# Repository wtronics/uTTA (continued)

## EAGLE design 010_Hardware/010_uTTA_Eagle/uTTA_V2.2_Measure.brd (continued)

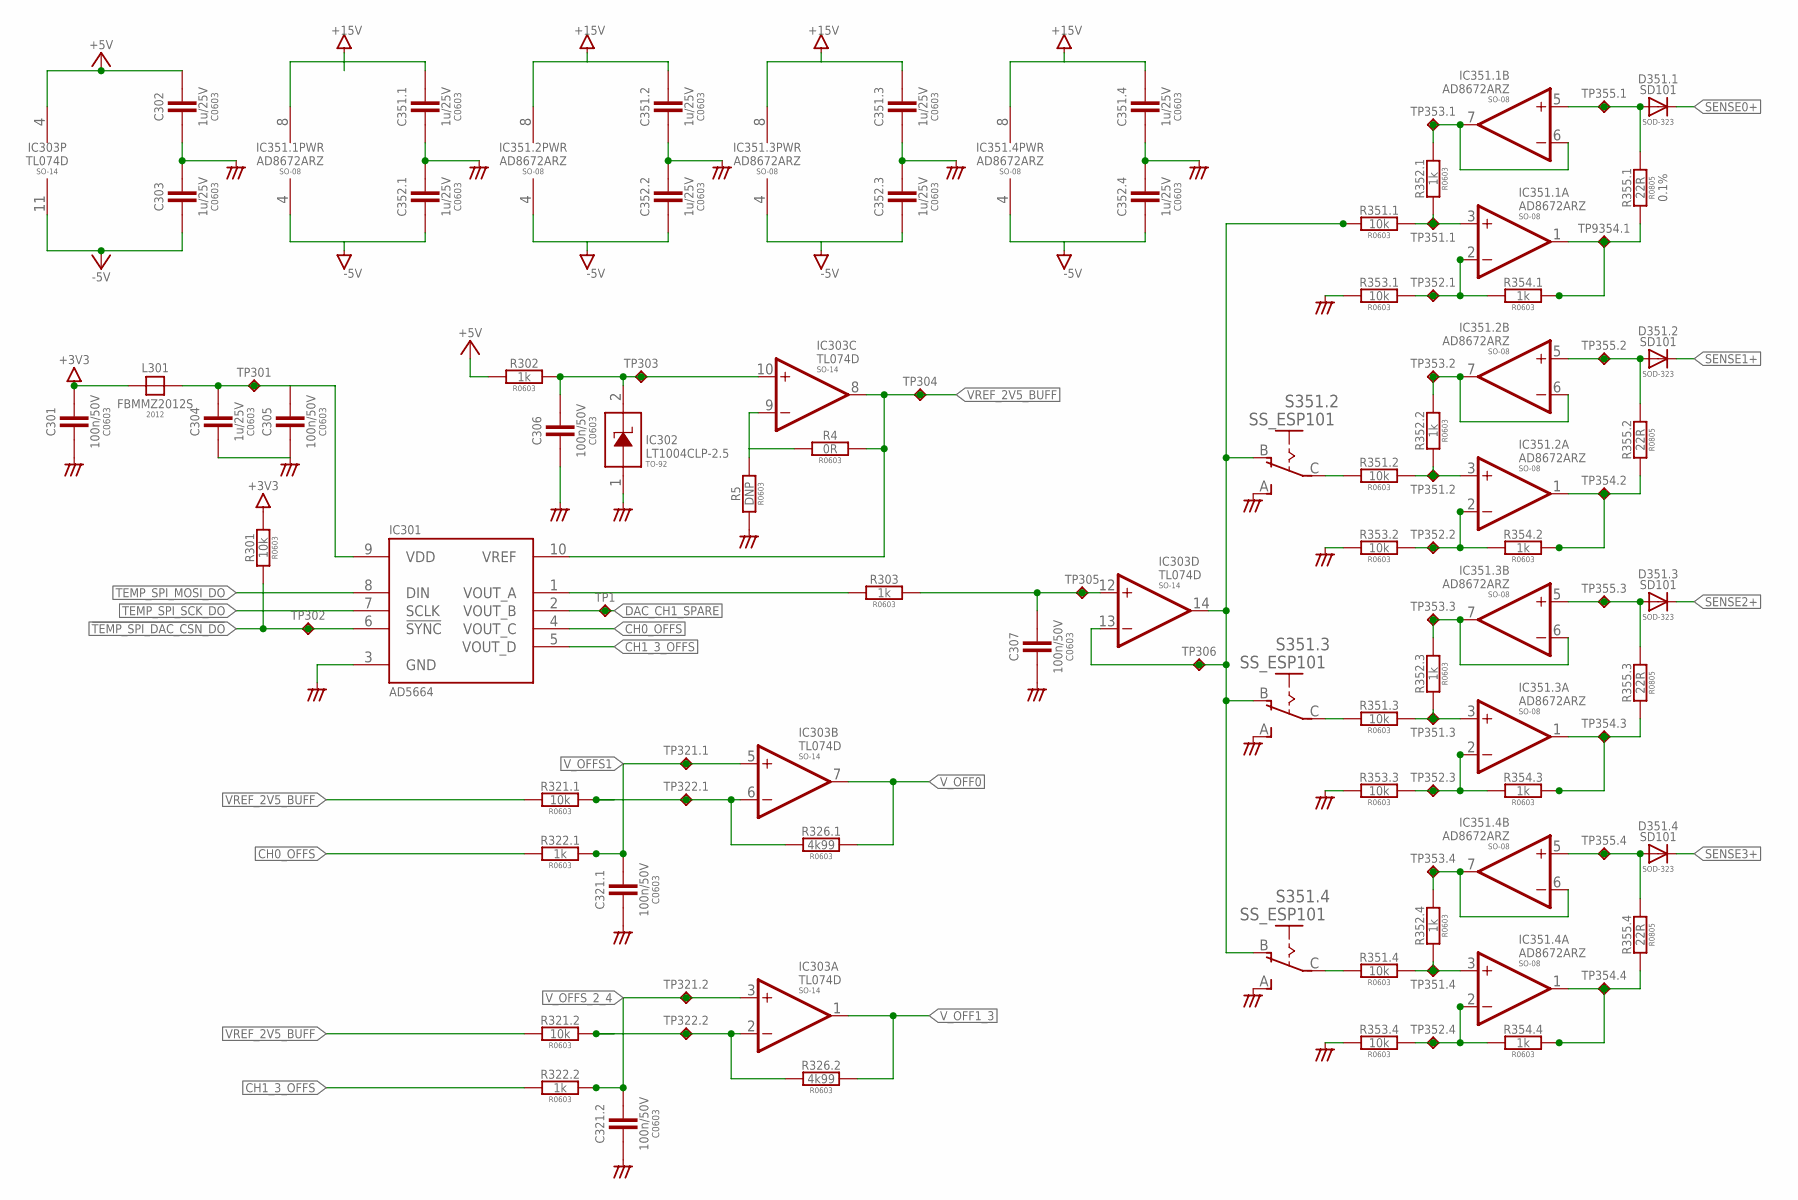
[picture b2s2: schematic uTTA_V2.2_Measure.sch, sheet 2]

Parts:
C301, C305, C306, C307, C321.1, C321.2: 100n/50V; C0603
C302, C303, C304, C351.1, C351.2, C351.3, C351.4, C352.1, C352.2, C352.3, C352.4: 1u/25V; C0603
D351.1, D351.2, D351.3, D351.4: SD101; SOD323-R
IC301: AD5664; MSOP10
IC302: LT1004CLP-2.5; TO92-
IC303: TL074D; SO14
IC351.1, IC351.2, IC351.3, IC351.4: AD8672ARZ; SO08
L301: FBMMZ2012S; FB2012
R4: 0R; R0603
R5: DNP; R0603
R301: 10k; R0603
R302, R303, R322.1, R322.2: 1k; R0603
R321.1, R321.2, R351.1, R351.2, R351.3, R351.4, R353.1, R353.2, R353.3, R353.4: 10k; R0603; TOLERANCE 0.1%
R326.1, R326.2: 4k99; R0603; TOLERANCE 0.1%
R352.1, R352.2, R352.3, R352.4, R354.1, R354.2, R354.3, R354.4: 1k; R0603; TOLERANCE 0.1%
R355.1, R355.2, R355.3, R355.4: 22R; R0805; TOLERANCE 0.1%
S351.2, S351.3, S351.4: SS_ESP101
TP1, TP301, TP302, TP304, TP306, TP321.1, TP321.2, TP322.1, TP322.2, TP351.1, TP351.2, TP351.3, TP351.4, TP352.1, TP352.2, TP352.3, TP352.4, TP353.1, TP353.2, TP353.3, TP353.4, TP354.2, TP354.3, TP354.4, TP355.1, TP355.2, TP355.3, TP355.4, TP9354.1: TPC90; C90
TP303, TP305: TPC90H30; C90H30

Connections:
3V3_DAC: C304.1, C305.1, IC301.9 (VDD), L301.2, TP301.P$1
!TEMP_SPI_DAC_CSN_DO: IC301.6 (!SYNC), R301.2, TP302.P$1; also elsewhere on the board
+3V3: C301.1, L301.1, R301.1; also elsewhere on the board
+5V: C302.1, IC303.4 (V+), R302.1; also elsewhere on the board
+15V: C351.1.1, C351.2.1, C351.3.1, C351.4.1, IC351.1.8 (V+), IC351.2.8 (V+), IC351.3.8 (V+), IC351.4.8 (V+); also elsewhere on the board
-5V: C303.2, C352.1.2, C352.2.2, C352.3.2, C352.4.2, IC303.11 (V-), IC351.1.4 (V-), IC351.2.4 (V-), IC351.3.4 (V-), IC351.4.4 (V-); also elsewhere on the board
AGND: C301.2, C302.2, C303.1, C304.2, C305.2, C306.2, C307.2, C321.1.2, C321.2.2, C351.1.2, C351.2.2, C351.3.2, C351.4.2, C352.1.1, C352.2.1, C352.3.1, C352.4.1, IC301.3 (GND), IC302.1 (A), R5.2, R353.1.1, R353.2.1, R353.3.1, R353.4.1, S351.2.A (S), S351.3.A (S), S351.4.A (S); also elsewhere on the board
CH0_OFFS: IC301.4 (VOUT_C), R322.1.1
CH1_3_OFFS: IC301.5 (VOUT_D), R322.2.1
DAC_CH1_SPARE: IC301.2 (VOUT_B), TP1.P$1
ISENS_SET: IC303.13 (-IN), IC303.14 (OUT), R351.1.1, S351.2.B (O), S351.3.B (O), S351.4.B (O), TP306.P$1
ISENS_SET_IN: C307.1, IC303.12 (+IN), R303.2, TP305.P$1
ISEN_FB1: D351.1.A, IC351.1.5 (+IN), R355.1.2, TP355.1.P$1
ISEN_FB2: D351.2.A, IC351.2.5 (+IN), R355.2.2, TP355.2.P$1
ISEN_FB3: D351.3.A, IC351.3.5 (+IN), R355.3.2, TP355.3.P$1
ISEN_FB4: D351.4.A, IC351.4.5 (+IN), R355.4.2, TP355.4.P$1
ISEN_FB_OUT1: IC351.1.6 (-IN), IC351.1.7 (OUT), R352.1.2, TP353.1.P$1
ISEN_FB_OUT2: IC351.2.6 (-IN), IC351.2.7 (OUT), R352.2.2, TP353.2.P$1
ISEN_FB_OUT3: IC351.3.6 (-IN), IC351.3.7 (OUT), R352.3.2, TP353.3.P$1
ISEN_FB_OUT4: IC351.4.6 (-IN), IC351.4.7 (OUT), R352.4.2, TP353.4.P$1
ISEN_FB_SUM1: IC351.1.2 (-IN), R353.1.2, R354.1.1, TP352.1.P$1
ISEN_FB_SUM2: IC351.2.2 (-IN), R353.2.2, R354.2.1, TP352.2.P$1
ISEN_FB_SUM3: IC351.3.2 (-IN), R353.3.2, R354.3.1, TP352.3.P$1
ISEN_FB_SUM4: IC351.4.2 (-IN), R353.4.2, R354.4.1, TP352.4.P$1
ISEN_OUT1: IC351.1.1 (OUT), R354.1.2, R355.1.1, TP9354.1.P$1
ISEN_OUT2: IC351.2.1 (OUT), R354.2.2, R355.2.1, TP354.2.P$1
ISEN_OUT3: IC351.3.1 (OUT), R354.3.2, R355.3.1, TP354.3.P$1
ISEN_OUT4: IC351.4.1 (OUT), R354.4.2, R355.4.1, TP354.4.P$1
ISEN_SET2: R351.2.1, S351.2.C
ISEN_SET3: R351.3.1, S351.3.C
ISEN_SET4: R351.4.1, S351.4.C
ISEN_SET_SUM1: IC351.1.3 (+IN), R351.1.2, R352.1.1, TP351.1.P$1
ISEN_SET_SUM2: IC351.2.3 (+IN), R351.2.2, R352.2.1, TP351.2.P$1
ISEN_SET_SUM3: IC351.3.3 (+IN), R351.3.2, R352.3.1, TP351.3.P$1
ISEN_SET_SUM4: IC351.4.3 (+IN), R351.4.2, R352.4.1, TP351.4.P$1
I_SENSE_DAC_SET: IC301.1 (VOUT_A), R303.1
unnamed: IC303.9 (-IN), R4.2, R5.1
SENSE0+: D351.1.C; also elsewhere on the board
SENSE1+: D351.2.C; also elsewhere on the board
SENSE2+: D351.3.C; also elsewhere on the board
SENSE3+: D351.4.C; also elsewhere on the board
TEMP_SPI_MOSI_DO: IC301.8 (DIN); also elsewhere on the board
TEMP_SPI_SCK_DO: IC301.7 (SCLK); also elsewhere on the board
VOFFS_RR1: IC303.6 (-IN), R321.1.1, R326.1.2, TP322.1.P$1
VOFFS_RR2_4: IC303.2 (-IN), R321.2.1, R326.2.2, TP322.2.P$1
VREF: C306.1, IC302.2 (C), IC303.10 (+IN), R302.2, TP303.P$1
VREF_2V5_BUFF: IC301.10 (VREF), IC303.8 (OUT), R4.1, R321.1.2, R321.2.2, TP304.P$1; also elsewhere on the board
V_OFF0: IC303.7 (OUT), R326.1.1; also elsewhere on the board
V_OFF1_3: IC303.1 (OUT), R326.2.1; also elsewhere on the board
V_OFFS1: C321.1.1, IC303.5 (+IN), R322.1.2, TP321.1.P$1
V_OFFS_2_4: C321.2.1, IC303.3 (+IN), R322.2.2, TP321.2.P$1

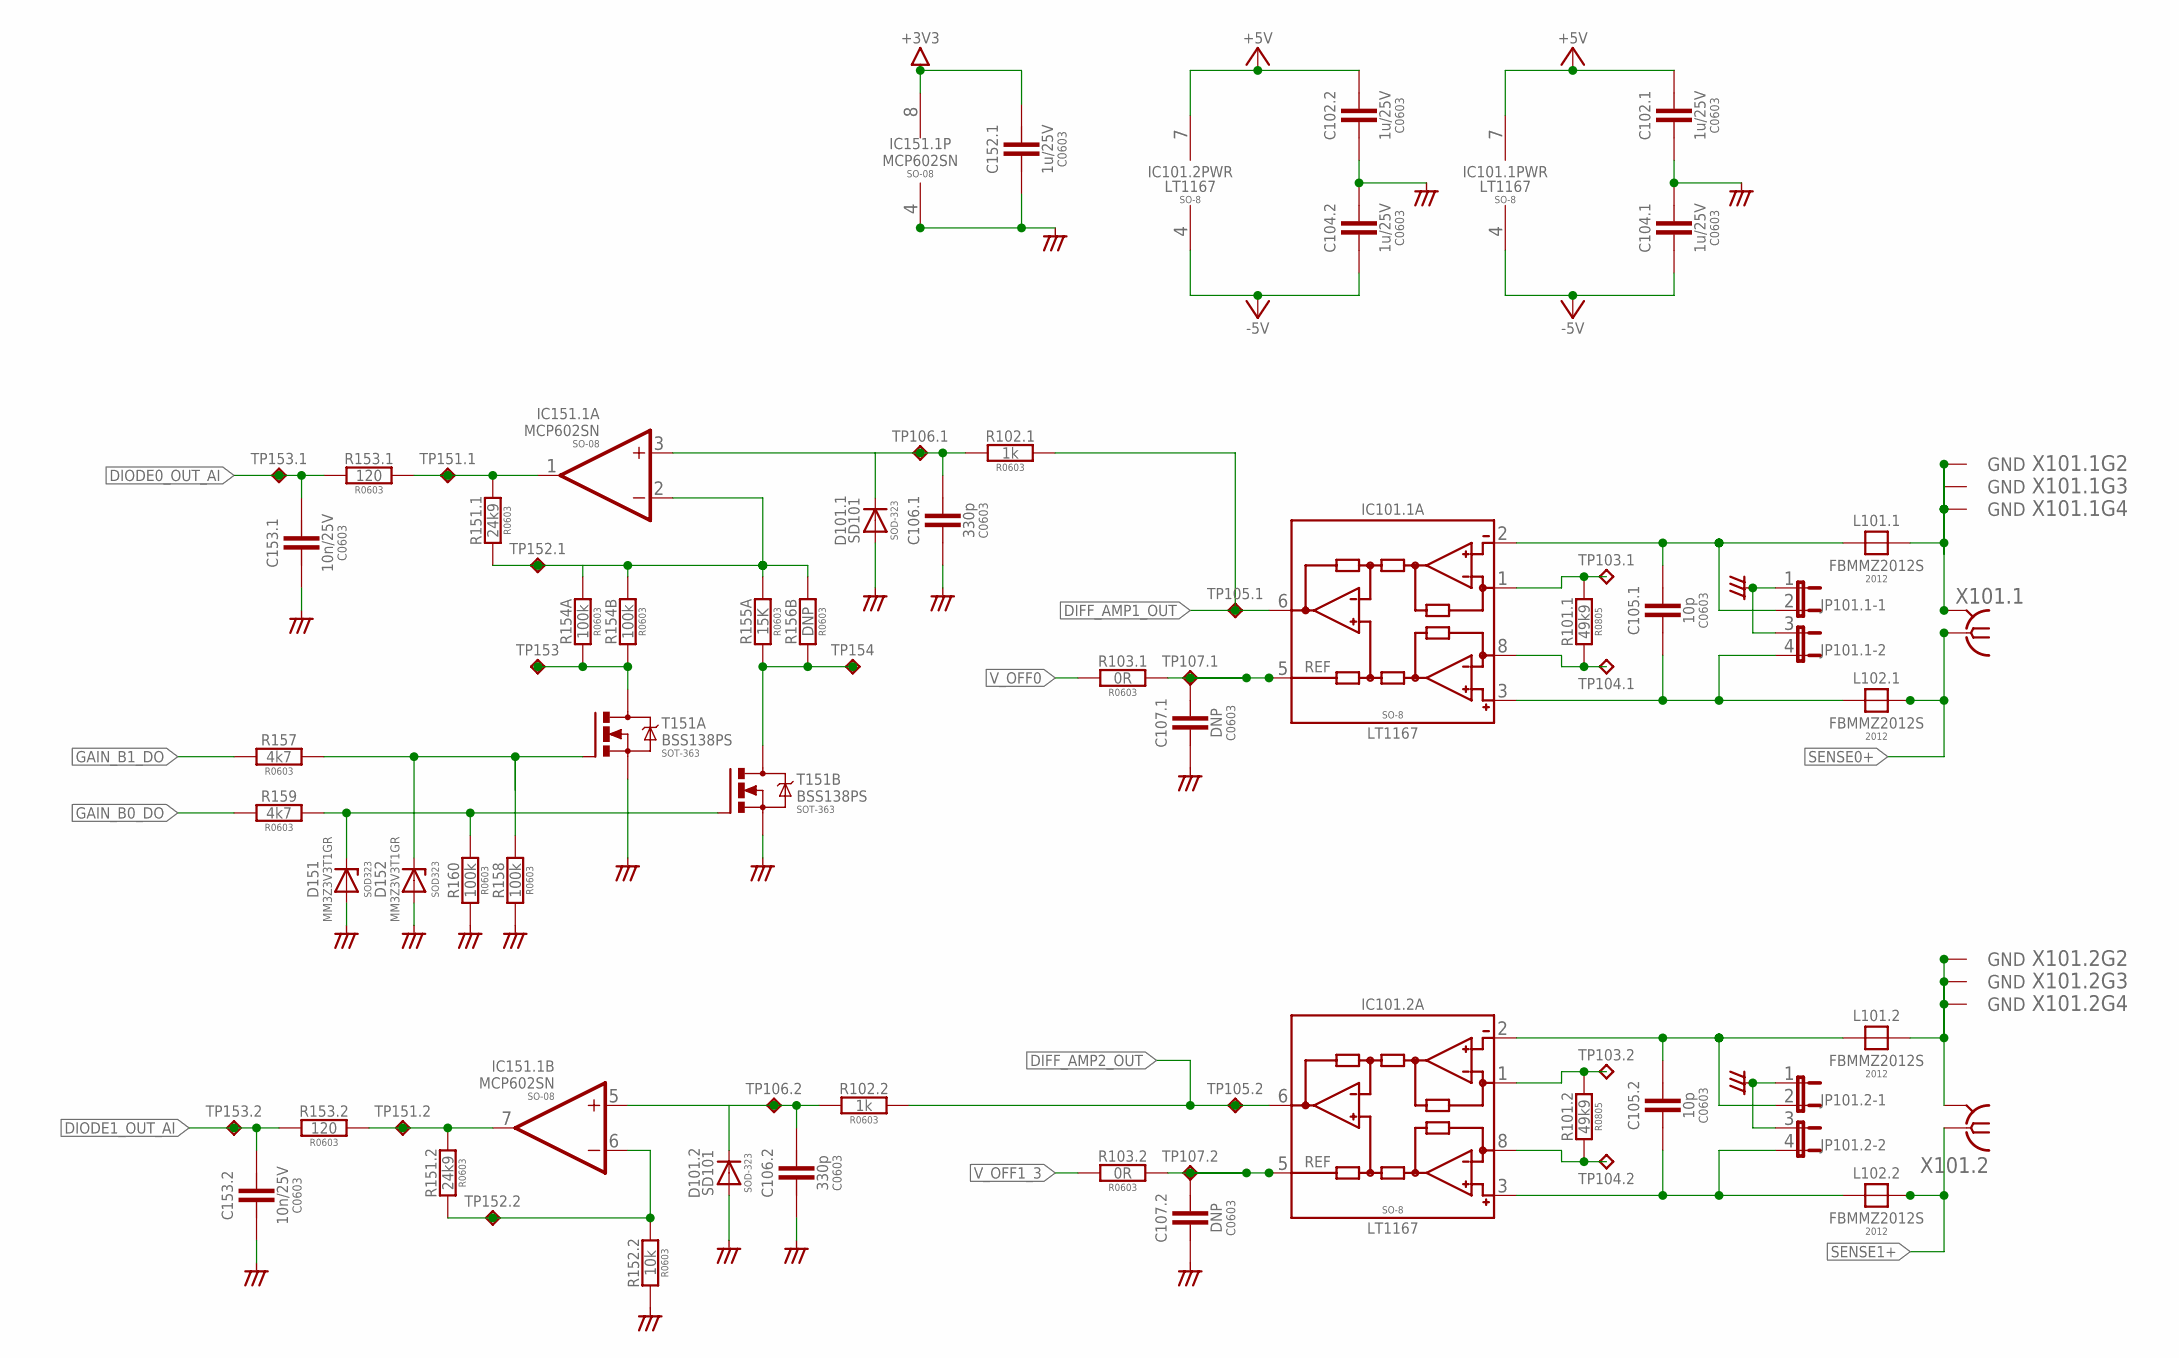
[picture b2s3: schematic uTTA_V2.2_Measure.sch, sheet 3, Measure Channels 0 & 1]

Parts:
C102.1, C102.2, C104.1, C104.2, C152.1: 1u/25V; C0603
C105.1, C105.2: 10p; C0603
C106.1, C106.2: 330p; C0603
C107.1, C107.2: DNP; C0603
C153.1, C153.2: 10n/25V; C0603
D101.1, D101.2: SD101; SOD323-R
D151, D152: MM3Z3V3T1GR; SOD323-R
IC101.1, IC101.2: LT1167; SO08
IC151.1: MCP602SN; SO08
JP101.1, JP101.2: JP2QE; JP2Q
L101.1, L101.2, L102.1, L102.2: FBMMZ2012S; FB2012
R101.1, R101.2: 49k9; R0805; TOLERANCE 0.1%
R102.1, R102.2: 1k; R0603
R103.1, R103.2: 0R; R0603
R151.1, R151.2: 24k9; R0603; TOLERANCE 0.1%
R152.2: 10k; R0603; TOLERANCE 0.1%
R153.1, R153.2: 120; R0603
R154A, R154B: 100k; R0603; TOLERANCE 0.1%
R155A: 15K; R0603; TOLERANCE 0.1%
R156B: DNP; R0603
R157, R159: 4k7; R0603
R158, R160: 100k; R0603
T151: BSS138PS; SOT363_PHILIPS
TP103.1, TP103.2, TP104.1, TP104.2, TP105.1, TP105.2, TP107.1, TP107.2, TP152.1, TP152.2, TP153, TP154: TPC90; C90
TP106.1, TP106.2, TP151.1, TP151.2, TP153.1, TP153.2: TPC90H30; C90H30
X101.1, X101.2: BU-SMA-GSPECIAL; BU_SMA_3P

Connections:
+3V3: C152.1.1, IC151.1.8 (V+); also elsewhere on the board
+5V: C102.1.1, C102.2.1, IC101.1.7 (V+), IC101.2.7 (V+); also elsewhere on the board
-5V: C104.1.2, C104.2.2, IC101.1.4 (V-), IC101.2.4 (V-); also elsewhere on the board
AGND: C102.1.2, C102.2.2, C104.1.1, C104.2.1, C106.1.2, C106.2.2, C107.1.2, C107.2.2, C152.1.2, C153.1.2, C153.2.2, D101.1.A, D101.2.A, D151.A, D152.A, IC151.1.4 (V-), JP101.1.1, JP101.1.3 (1), JP101.2.1, JP101.2.3 (1), R152.2.1, R158.1, R160.1, T151.1 (S), T151.4 (S); also elsewhere on the board
AMP1_OUT: IC151.1.1 (OUT), R151.1.2, R153.1.2, TP151.1.P$1
AMP1_RG_B0: R155A.1, R156B.1, T151.6 (D), TP154.P$1
AMP1_RG_B1: R154A.1, R154B.1, T151.3 (D), TP153.P$1
AMP2_FB: IC151.1.6 (-IN), R151.2.1, R152.2.2, TP152.2.P$1
AMP2_OUT: IC151.1.7 (OUT), R151.2.2, R153.2.2, TP151.2.P$1
B0_GATE: D151.C, R159.2, R160.2, T151.5 (G)
B1_GATE: D152.C, R157.2, R158.2, T151.2 (G)
DIFF_AMP1_OUT: IC101.1.6 (OUT), R102.1.2, TP105.1.P$1
DIFF_AMP2_OUT: IC101.2.6 (OUT), R102.2.2, TP105.2.P$1
DIODE0_OUT_AI: C153.1.1, R153.1.1, TP153.1.P$1; also elsewhere on the board
DIODE1_OUT_AI: C153.2.1, R153.2.1, TP153.2.P$1; also elsewhere on the board
DIODE2_IN: C106.2.1, D101.2.C, IC151.1.5 (+IN), R102.2.1, TP106.2.P$1
GAIN1+: IC101.1.8 (RG), R101.1.2, TP104.1.P$1
GAIN1-: IC101.1.1 (RG), R101.1.1, TP103.1.P$1
GAIN2+: IC101.2.8 (RG), R101.2.2, TP104.2.P$1
GAIN2-: IC101.2.1 (RG), R101.2.1, TP103.2.P$1
GAIN_B0_DO: R159.1; also elsewhere on the board
GAIN_B1_DO: R157.1; also elsewhere on the board
IN1+: C105.1.2, IC101.1.3 (+IN), JP101.1.4 (2), L102.1.1
IN1-: C105.1.1, IC101.1.2 (-IN), JP101.1.2, L101.1.1
IN2+: C105.2.2, IC101.2.3 (+IN), JP101.2.4 (2), L102.2.1
IN2-: C105.2.1, IC101.2.2 (-IN), JP101.2.2, L101.2.1
PGA_DIODE1_IN: C106.1.1, D101.1.C, IC151.1.3 (+IN), R102.1.1, TP106.1.P$1
SENSE0+: L102.1.2, X101.1.C1 (1), X101.1.C2 (1); also elsewhere on the board
SENSE1+: L102.2.2, X101.2.C1 (1), X101.2.C2 (1); also elsewhere on the board
SENSE1-: L101.1.2, X101.1.@GND1 (GND), X101.1.@GND2 (GND), X101.1.@GND3 (GND), X101.1.@GND4 (GND), X101.1.GND
SENSE2-: L101.2.2, X101.2.@GND1 (GND), X101.2.@GND2 (GND), X101.2.@GND3 (GND), X101.2.@GND4 (GND), X101.2.GND
TP152.1: IC151.1.2 (-IN), R151.1.1, R154A.2, R154B.2, R155A.2, R156B.2, TP152.1.P$1
V_OFF0: R103.1.1; also elsewhere on the board
V_OFF1_3: R103.2.1; also elsewhere on the board
V_OPREF1: C107.1.1, IC101.1.5 (REF), R103.1.2, TP107.1.P$1
V_OPREF2: C107.2.1, IC101.2.5 (REF), R103.2.2, TP107.2.P$1

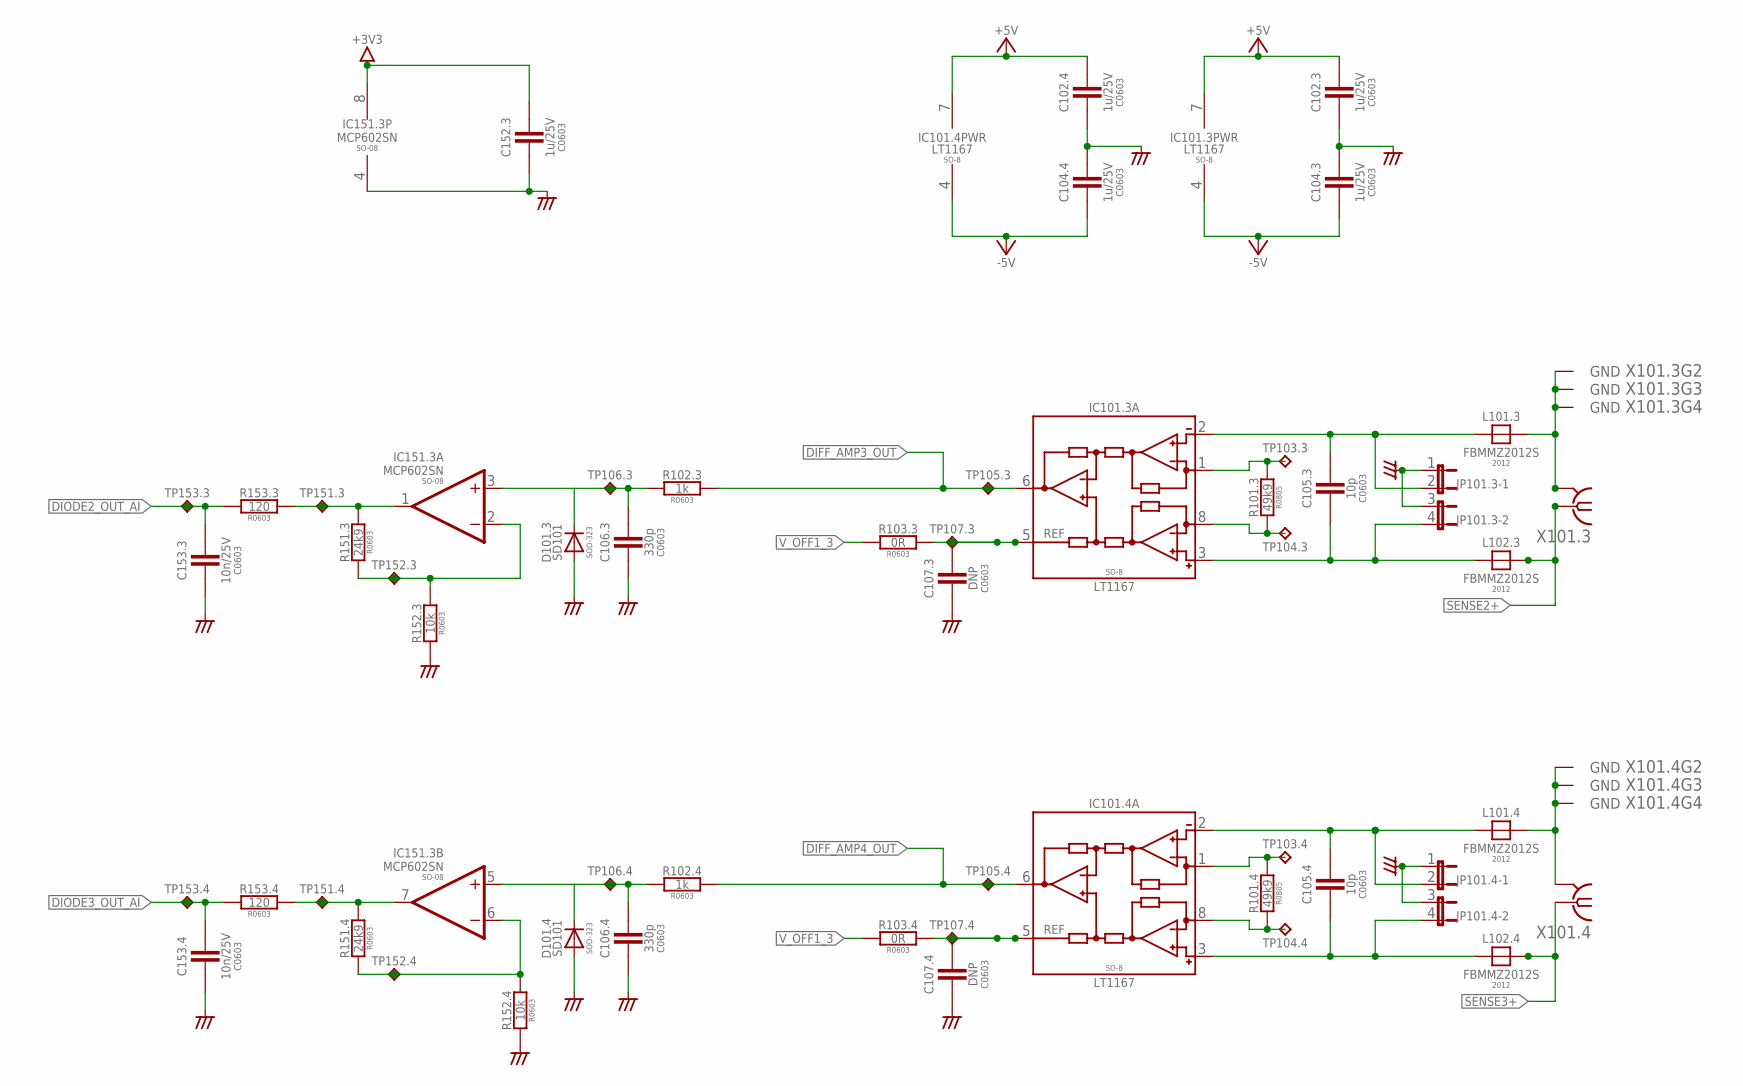
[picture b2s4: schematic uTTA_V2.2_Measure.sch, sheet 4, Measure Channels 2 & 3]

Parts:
C102.3, C102.4, C104.3, C104.4, C152.3: 1u/25V; C0603
C105.3, C105.4: 10p; C0603
C106.3, C106.4: 330p; C0603
C107.3, C107.4: DNP; C0603
C153.3, C153.4: 10n/25V; C0603
D101.3, D101.4: SD101; SOD323-R
IC101.3, IC101.4: LT1167; SO08
IC151.3: MCP602SN; SO08
JP101.3, JP101.4: JP2QE; JP2Q
L101.3, L101.4, L102.3, L102.4: FBMMZ2012S; FB2012
R101.3, R101.4: 49k9; R0805; TOLERANCE 0.1%
R102.3, R102.4: 1k; R0603
R103.3, R103.4: 0R; R0603
R151.3, R151.4: 24k9; R0603; TOLERANCE 0.1%
R152.3, R152.4: 10k; R0603; TOLERANCE 0.1%
R153.3, R153.4: 120; R0603
TP103.3, TP103.4, TP104.3, TP104.4, TP105.3, TP105.4, TP107.3, TP107.4: TPC90; C90
TP106.3, TP106.4, TP151.3, TP151.4, TP152.3, TP152.4, TP153.3, TP153.4: TPC90H30; C90H30
X101.3, X101.4: BU-SMA-GSPECIAL; BU_SMA_3P

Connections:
+3V3: C152.3.1, IC151.3.8 (V+); also elsewhere on the board
+5V: C102.3.1, C102.4.1, IC101.3.7 (V+), IC101.4.7 (V+); also elsewhere on the board
-5V: C104.3.2, C104.4.2, IC101.3.4 (V-), IC101.4.4 (V-); also elsewhere on the board
AGND: C102.3.2, C102.4.2, C104.3.1, C104.4.1, C106.3.2, C106.4.2, C107.3.2, C107.4.2, C152.3.2, C153.3.2, C153.4.2, D101.3.A, D101.4.A, IC151.3.4 (V-), JP101.3.1, JP101.3.3 (1), JP101.4.1, JP101.4.3 (1), R152.3.1, R152.4.1; also elsewhere on the board
AMP3_FB: IC151.3.2 (-IN), R151.3.1, R152.3.2, TP152.3.P$1
AMP3_OUT: IC151.3.1 (OUT), R151.3.2, R153.3.2, TP151.3.P$1
AMP4_FB: IC151.3.6 (-IN), R151.4.1, R152.4.2, TP152.4.P$1
AMP4_OUT: IC151.3.7 (OUT), R151.4.2, R153.4.2, TP151.4.P$1
DIFF_AMP3_OUT: IC101.3.6 (OUT), R102.3.2, TP105.3.P$1
DIFF_AMP4_OUT: IC101.4.6 (OUT), R102.4.2, TP105.4.P$1
DIODE2_OUT_AI: C153.3.1, R153.3.1, TP153.3.P$1; also elsewhere on the board
DIODE3_IN: C106.3.1, D101.3.C, IC151.3.3 (+IN), R102.3.1, TP106.3.P$1
DIODE3_OUT_AI: C153.4.1, R153.4.1, TP153.4.P$1; also elsewhere on the board
DIODE4_IN: C106.4.1, D101.4.C, IC151.3.5 (+IN), R102.4.1, TP106.4.P$1
GAIN3+: IC101.3.8 (RG), R101.3.2, TP104.3.P$1
GAIN3-: IC101.3.1 (RG), R101.3.1, TP103.3.P$1
GAIN4+: IC101.4.8 (RG), R101.4.2, TP104.4.P$1
GAIN4-: IC101.4.1 (RG), R101.4.1, TP103.4.P$1
IN3+: C105.3.2, IC101.3.3 (+IN), JP101.3.4 (2), L102.3.1
IN3-: C105.3.1, IC101.3.2 (-IN), JP101.3.2, L101.3.1
IN4+: C105.4.2, IC101.4.3 (+IN), JP101.4.4 (2), L102.4.1
IN4-: C105.4.1, IC101.4.2 (-IN), JP101.4.2, L101.4.1
SENSE2+: L102.3.2, X101.3.C1 (1), X101.3.C2 (1); also elsewhere on the board
SENSE3+: L102.4.2, X101.4.C1 (1), X101.4.C2 (1); also elsewhere on the board
SENSE3-: L101.3.2, X101.3.@GND1 (GND), X101.3.@GND2 (GND), X101.3.@GND3 (GND), X101.3.@GND4 (GND), X101.3.GND
SENSE4-: L101.4.2, X101.4.@GND1 (GND), X101.4.@GND2 (GND), X101.4.@GND3 (GND), X101.4.@GND4 (GND), X101.4.GND
V_OFF1_3: R103.3.1, R103.4.1; also elsewhere on the board
V_OPREF3: C107.3.1, IC101.3.5 (REF), R103.3.2, TP107.3.P$1
V_OPREF4: C107.4.1, IC101.4.5 (REF), R103.4.2, TP107.4.P$1

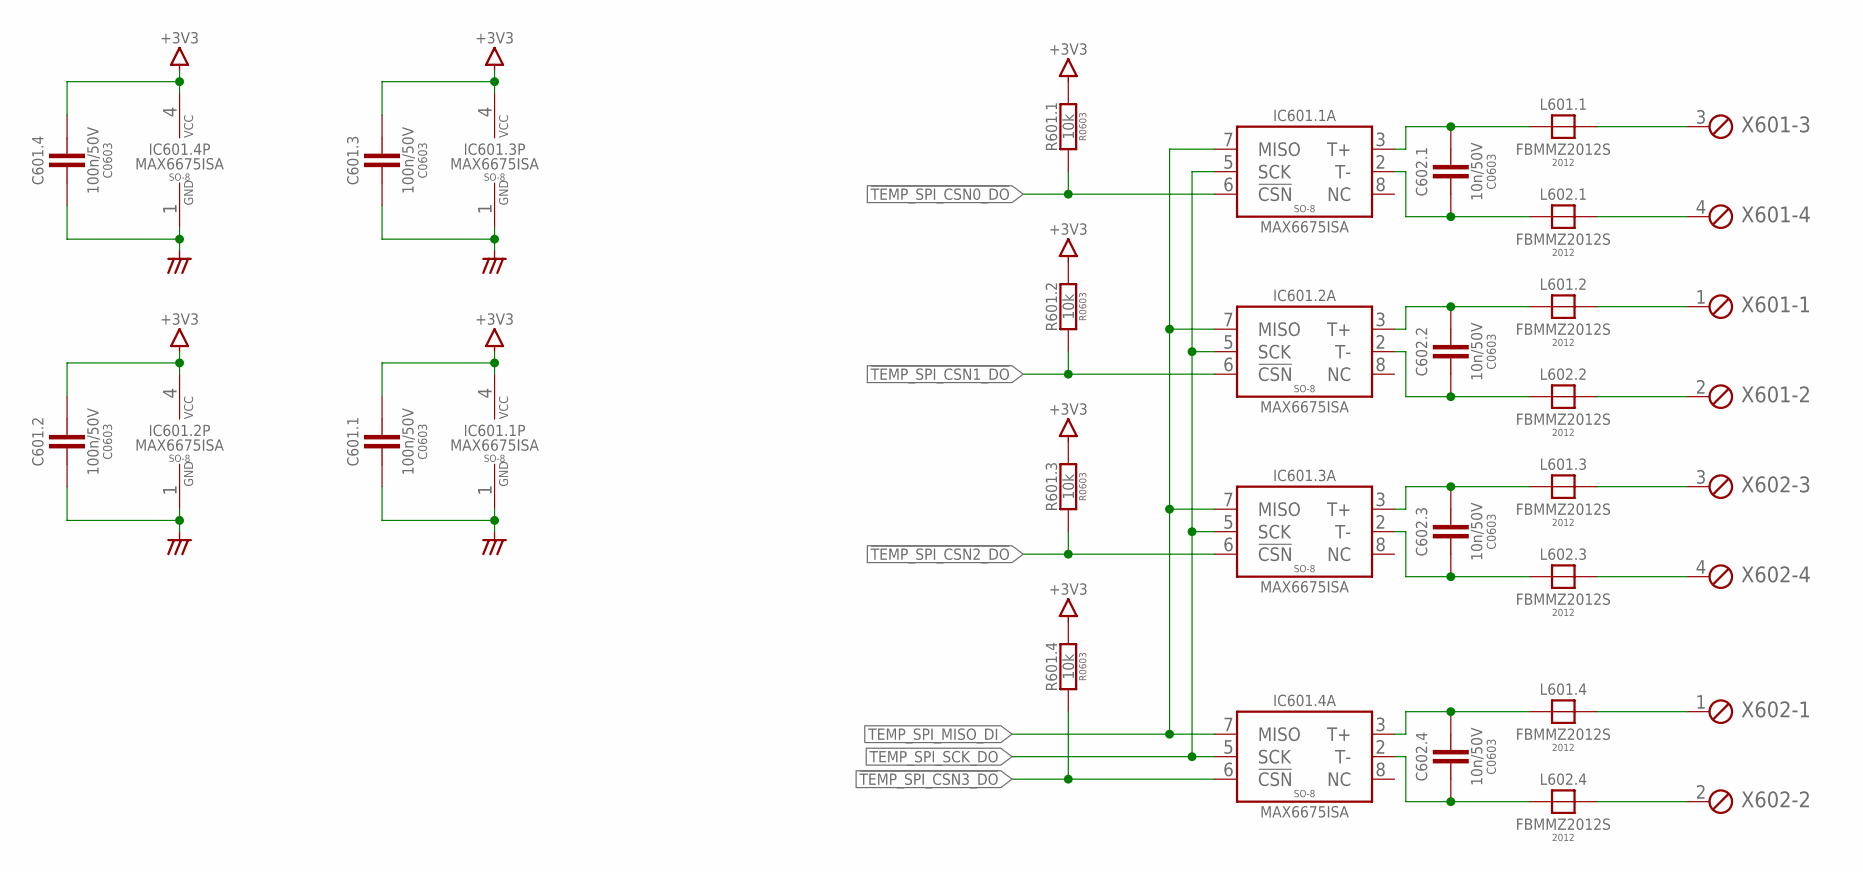
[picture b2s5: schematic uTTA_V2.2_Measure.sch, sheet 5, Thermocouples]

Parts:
C601.1, C601.2, C601.3, C601.4: 100n/50V; C0603
C602.1, C602.2, C602.3, C602.4: 10n/50V; C0603
IC601.1, IC601.2, IC601.3, IC601.4: MAX6675ISA; SO08
L601.1, L601.2, L601.3, L601.4, L602.1, L602.2, L602.3, L602.4: FBMMZ2012S; FB2012
R601.1, R601.2, R601.3, R601.4: 10k; R0603
X601, X602: MPT4; 4POL254

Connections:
!TEMP_SPI_CSN0_DO: IC601.1.6 (!CSN), R601.1.2; also elsewhere on the board
!TEMP_SPI_CSN1_DO: IC601.2.6 (!CSN), R601.2.2; also elsewhere on the board
!TEMP_SPI_CSN2_DO: IC601.3.6 (!CSN), R601.3.2; also elsewhere on the board
!TEMP_SPI_CSN3_DO: IC601.4.6 (!CSN), R601.4.2; also elsewhere on the board
+3V3: C601.1.1, C601.2.1, C601.3.1, C601.4.1, IC601.1.4 (VCC), IC601.2.4 (VCC), IC601.3.4 (VCC), IC601.4.4 (VCC), R601.1.1, R601.2.1, R601.3.1, R601.4.1; also elsewhere on the board
AGND: C601.1.2, C601.2.2, C601.3.2, C601.4.2, IC601.1.1 (GND), IC601.2.1 (GND), IC601.3.1 (GND), IC601.4.1 (GND); also elsewhere on the board
TC1+: L601.4.2, X602.1
TC1-: L602.4.2, X602.2
TC2+: L601.3.2, X602.3
TC2-: L602.3.2, X602.4
TC3+: L601.2.2, X601.1
TC3-: L602.2.2, X601.2
TC4+: L601.1.2, X601.3
TC4-: L602.1.2, X601.4
TEMP_SPI_MISO_DI: IC601.1.7 (MISO), IC601.2.7 (MISO), IC601.3.7 (MISO), IC601.4.7 (MISO); also elsewhere on the board
TEMP_SPI_SCK_DO: IC601.1.5 (SCK), IC601.2.5 (SCK), IC601.3.5 (SCK), IC601.4.5 (SCK); also elsewhere on the board
TK1_N: C602.4.2, IC601.4.2 (T-), L602.4.1
TK1_P: C602.4.1, IC601.4.3 (T+), L601.4.1
TK2_N: C602.3.2, IC601.3.2 (T-), L602.3.1
TK2_P: C602.3.1, IC601.3.3 (T+), L601.3.1
TK3_N: C602.2.2, IC601.2.2 (T-), L602.2.1
TK3_P: C602.2.1, IC601.2.3 (T+), L601.2.1
TK4_N: C602.1.2, IC601.1.2 (T-), L602.1.1
TK4_P: C602.1.1, IC601.1.3 (T+), L601.1.1

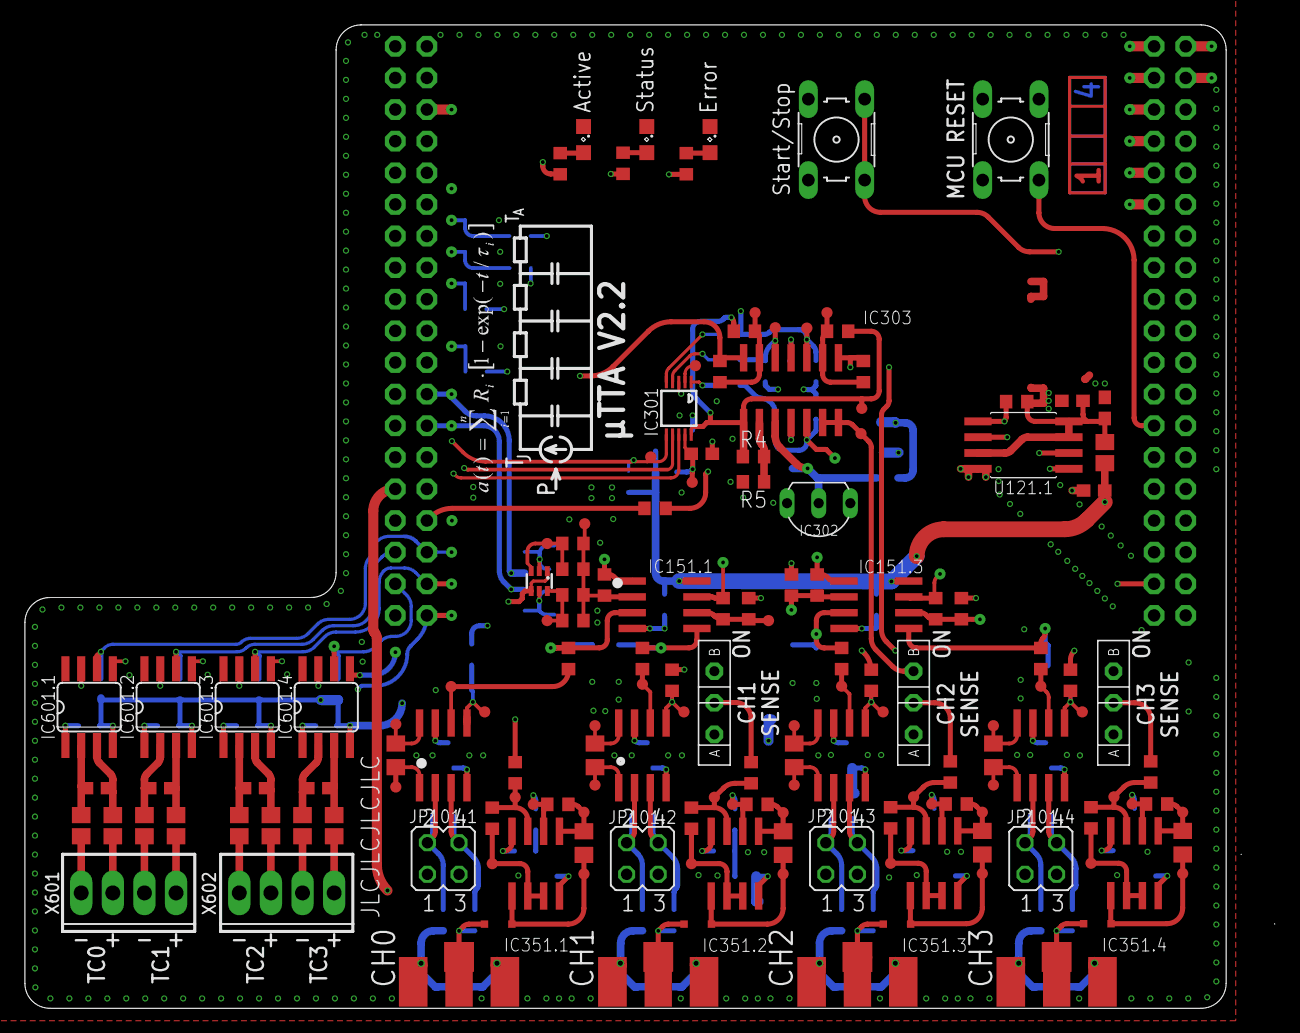
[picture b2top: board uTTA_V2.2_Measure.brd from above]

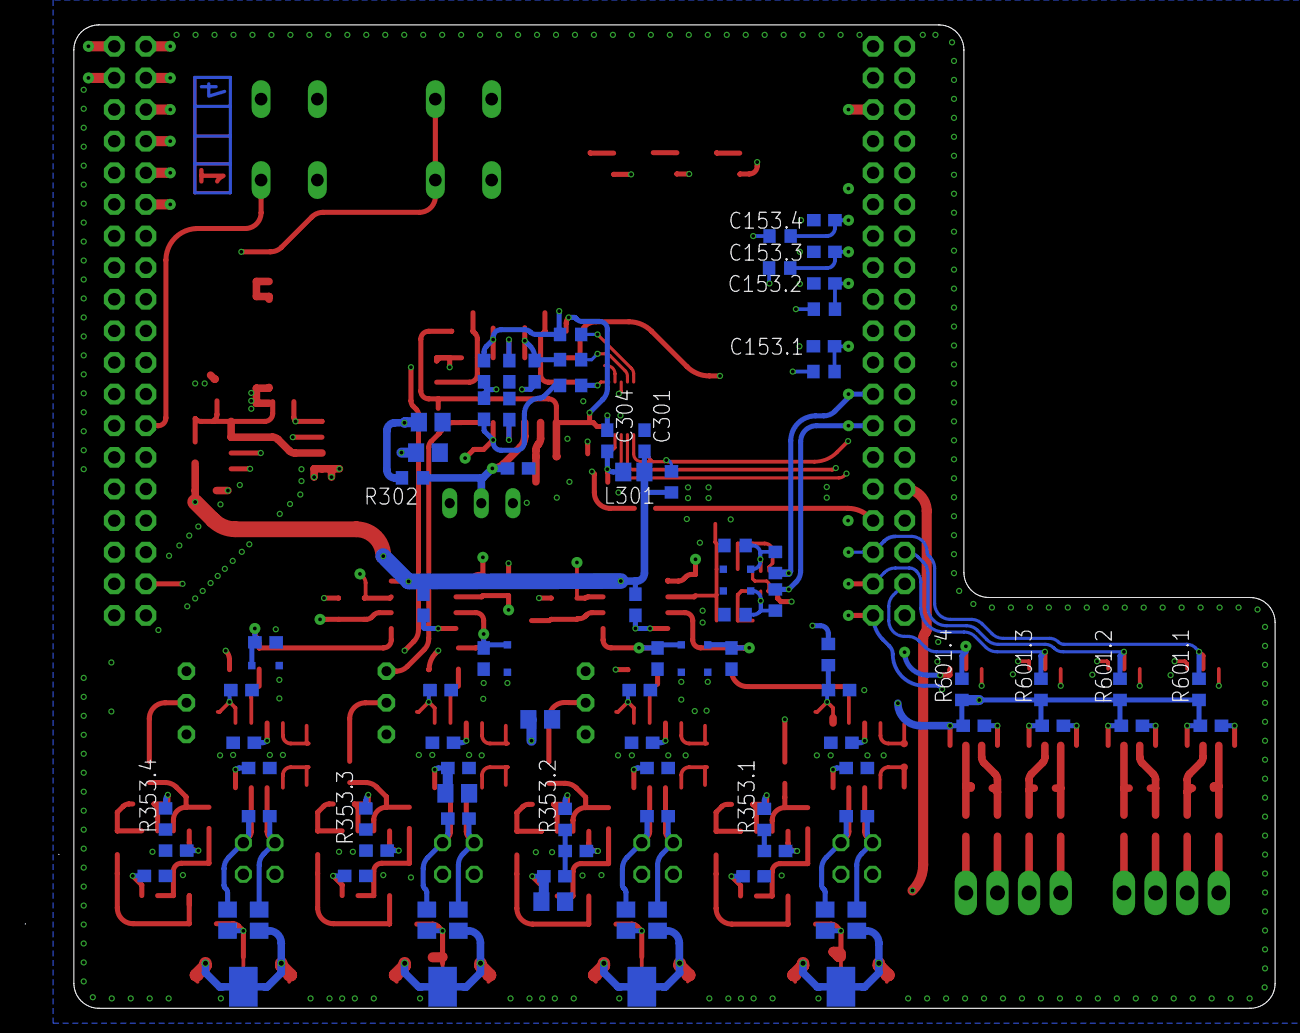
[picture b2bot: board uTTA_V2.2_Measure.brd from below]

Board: 4 copper layers, 100.4 x 79.0 mm, 280 parts (88 on the bottom side), 145 nets.

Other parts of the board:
U$1: A4_LOC_CC_BY_NC_SA
